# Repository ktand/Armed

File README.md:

# Armed 3D Printer Controller

## Features

* 32bit STM32F407VET6 
  * 168MHz 
  * 512kB Flash 
  * 192kB RAM 
* Power supply from 12-24V 
* Dual power inputs with separate fuses 
  * One for one of the high current outputs and the other one for the rest 
* Up to 5 steppers 
  * Dual outputs for one stepper for use with dual stepper Z-axis 
* 3 high current outputs 
* 3 fan outputs 
* 3 temperature sensors inputs 
* 3 endstops inputs 
* Filament runout detection 
* LCD display header 
* USB support 
* 10 extension pins 
* Support for TMC2130 SPI 
* 12-24V supply 
* I2C, SPI and UART extension ports 
* SWD header 
* Stepper configuration using solder jumpers 
* Einsy Rambo Form Factor (100x71mm) 

## Schematic and PCB Design

Designed using [Kicad 5.0](http://kicad.org/).

## Compatibilty

Arduino compatbile using the [Arduino Core STM32](https://github.com/stm32duino/Arduino_Core_STM32) and working with the [Marlin 2.0 3D printer firmware](https://github.com/MarlinFirmware/Marlin/tree/bugfix-2.0.x).

## Board configuration and pinout

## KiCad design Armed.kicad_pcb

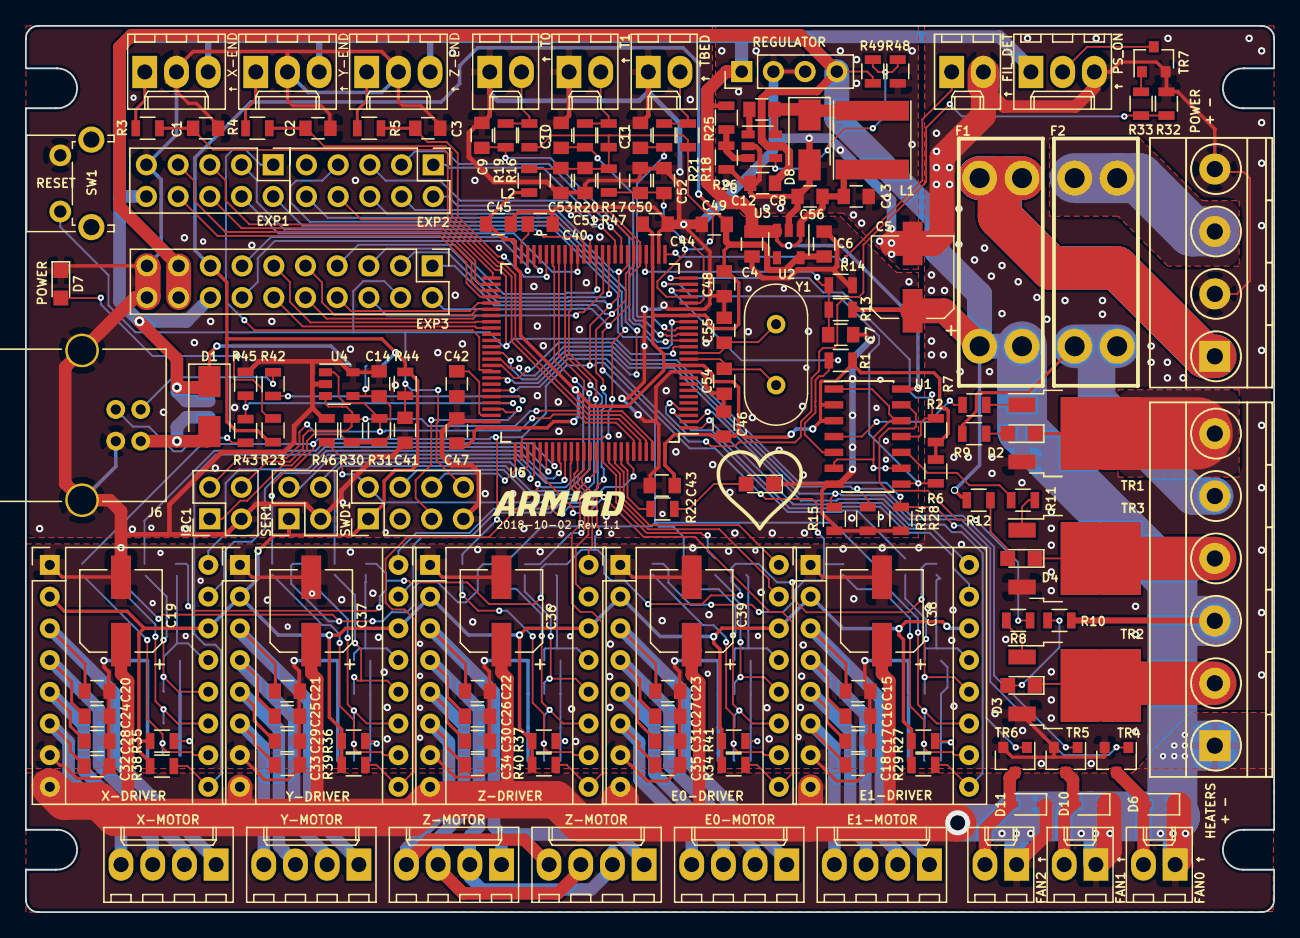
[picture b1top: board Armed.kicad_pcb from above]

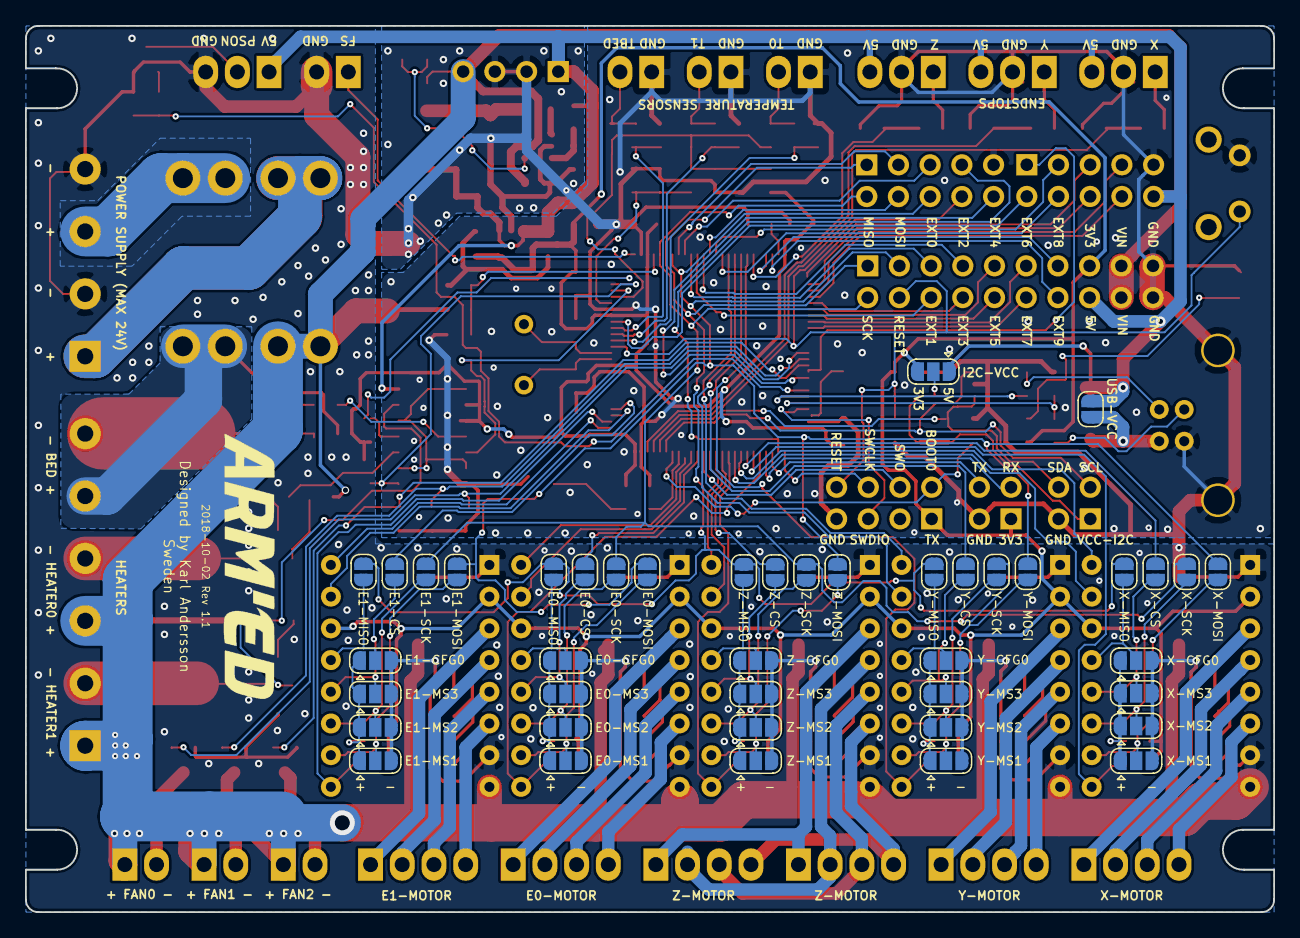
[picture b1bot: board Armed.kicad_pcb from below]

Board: 2 copper layers, 100.0 x 71.0 mm, 207 parts (42 on the bottom side), 165 nets.

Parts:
A1, A2, A3, A4, A5: Pololu_Breakout_A4988; Pololu_Breakout-16_15.2x20.3mm
C1, C2, C3: 10nF; C_0805
C4, C6: 1uF 16V X7R/X5R; C_0805
C5, C19, C36, C37, C38, C39: 100uF 35V; CP_Elec_6.3x5.8
C7, C12, C14, C41, C43, C44, C45, C46, C47, C48, C52, C53, C56: 100nF; C_0805
C8: 10uF 35V (X5R/X7R); C_0805
C9, C10, C11, C40, C42: 2.2uF; C_0805
C13: 10uF 16V (X5R/X7R); C_0805
C15, C16, C17, C18, C20, C21, C22, C23, C24, C25, C26, C27, C28, C29, C30, C31, C32, C33, C34, C35: 1nF; C_0805
C49: 10uF; C_0805
C50, C51: 1uF; C_0805
C54, C55: 20pF; C_0805
D1: BAT60J; D_SMA
D2, D3, D4, D5, D7: LED; LED_0805
D6, D10, D11: 1N4148WS; D_SOD-323
D8: B140-13-F; D_SMA
E0-MOT1, E1-MOT1: Conn_01x04_Male; Molex_KK-6410-04_04x2.54mm_Straight
EXP1, EXP2: Conn_02x05_Odd_Even; Pin_Header_Straight_2x05_Pitch2.54mm
EXP3: Conn_02x10_Odd_Even; Pin_Header_Straight_2x10_Pitch2.54mm
F1, F2: 3557-2; KEYSTONE-FUSE-3557-2
FAN1, FAN2, FAN3: Conn_01x02; Molex_KK-6410-02_02x2.54mm_Straight
FIL_DET1: Conn_01x02; Molex_KK-6410-02_02x2.54mm_Straight
I2C1: Conn_01x04; Pin_Header_Straight_2x02_Pitch2.54mm
J1: Conn_01x06; TerminalBlock_Phoenix_MKDS1.5-6pol
J2: Conn_01x04; TerminalBlock_Phoenix_MKDS1.5-4pol
J3, J4, J5: Conn_01x03; Molex_KK-6410-03_03x2.54mm_Straight
J6: USB_B
J7: Conn_01x04; Pin_Header_Straight_1x04_Pitch2.54mm
JP1: USB-VCC; SolderJumper-2_P1.3mm_Open_RoundedPad1.0x1.5mm
JP2: E1-MISO; SolderJumper-2_P1.3mm_Open_RoundedPad1.0x1.5mm
JP3: E1-MOSI; SolderJumper-2_P1.3mm_Open_RoundedPad1.0x1.5mm
JP4: E1-SCK; SolderJumper-2_P1.3mm_Open_RoundedPad1.0x1.5mm
JP5: E1-CS; SolderJumper-2_P1.3mm_Open_RoundedPad1.0x1.5mm
JP6: E1-CFG0; SolderJumper-3_P1.3mm_Open_RoundedPad1.0x1.5mm
JP7: E1-MS1; SolderJumper-3_P1.3mm_Open_RoundedPad1.0x1.5mm
JP8: E1-MS2; SolderJumper-3_P1.3mm_Open_RoundedPad1.0x1.5mm
JP9: E1-MS3; SolderJumper-3_P1.3mm_Open_RoundedPad1.0x1.5mm
JP10: E0-MISO; SolderJumper-2_P1.3mm_Open_RoundedPad1.0x1.5mm
JP11: E0-MOSI; SolderJumper-2_P1.3mm_Open_RoundedPad1.0x1.5mm
JP12: E0-SCK; SolderJumper-2_P1.3mm_Open_RoundedPad1.0x1.5mm
JP13: E0-CS; SolderJumper-2_P1.3mm_Open_RoundedPad1.0x1.5mm
JP14: X-MISO; SolderJumper-2_P1.3mm_Open_RoundedPad1.0x1.5mm
JP15: X-MOSI; SolderJumper-2_P1.3mm_Open_RoundedPad1.0x1.5mm
JP16: X-SCK; SolderJumper-2_P1.3mm_Open_RoundedPad1.0x1.5mm
JP17: X-CS; SolderJumper-2_P1.3mm_Open_RoundedPad1.0x1.5mm
JP18: Y-MISO; SolderJumper-2_P1.3mm_Open_RoundedPad1.0x1.5mm
JP19: Y-MOSI; SolderJumper-2_P1.3mm_Open_RoundedPad1.0x1.5mm
JP20: Y-SCK; SolderJumper-2_P1.3mm_Open_RoundedPad1.0x1.5mm
JP21: Y-CS; SolderJumper-2_P1.3mm_Open_RoundedPad1.0x1.5mm
JP22: Z-MISO; SolderJumper-2_P1.3mm_Open_RoundedPad1.0x1.5mm
JP23: Z-MOSI; SolderJumper-2_P1.3mm_Open_RoundedPad1.0x1.5mm
JP24: Z-SCK; SolderJumper-2_P1.3mm_Open_RoundedPad1.0x1.5mm
JP25: Z-CS; SolderJumper-2_P1.3mm_Open_RoundedPad1.0x1.5mm
JP26: E0-CFG0; SolderJumper-3_P1.3mm_Open_RoundedPad1.0x1.5mm
JP27: X-CFG0; SolderJumper-3_P1.3mm_Open_RoundedPad1.0x1.5mm
JP28: Y-CFG0; SolderJumper-3_P1.3mm_Open_RoundedPad1.0x1.5mm
JP29: Z-CFG0; SolderJumper-3_P1.3mm_Open_RoundedPad1.0x1.5mm
JP30: E0-MS1; SolderJumper-3_P1.3mm_Open_RoundedPad1.0x1.5mm
JP31: X-MS1; SolderJumper-3_P1.3mm_Open_RoundedPad1.0x1.5mm
JP32: Y-MS1; SolderJumper-3_P1.3mm_Open_RoundedPad1.0x1.5mm
JP33: Z-MS1; SolderJumper-3_P1.3mm_Open_RoundedPad1.0x1.5mm
JP34: X-MS2; SolderJumper-3_P1.3mm_Open_RoundedPad1.0x1.5mm
JP35: Y-MS2; SolderJumper-3_P1.3mm_Open_RoundedPad1.0x1.5mm
JP36: Z-MS2; SolderJumper-3_P1.3mm_Open_RoundedPad1.0x1.5mm
JP37: E0-MS2; SolderJumper-3_P1.3mm_Open_RoundedPad1.0x1.5mm
JP38: X-MS3; SolderJumper-3_P1.3mm_Open_RoundedPad1.0x1.5mm
JP39: Y-MS3; SolderJumper-3_P1.3mm_Open_RoundedPad1.0x1.5mm
JP40: Z-MS3; SolderJumper-3_P1.3mm_Open_RoundedPad1.0x1.5mm
JP41: E0-MS3; SolderJumper-3_P1.3mm_Open_RoundedPad1.0x1.5mm
JP42: I2C-VCC; SolderJumper-3_P1.3mm_Open_RoundedPad1.0x1.5mm
L1: 22uH NR6028T220M; L_Taiyo-Yuden_NR-60xx
L2: 7427920415; L_0805
PS_ON1: Conn_01x03; Molex_KK-6410-03_03x2.54mm_Straight
R1, R2, R6: 33k; R_0805
R3, R4, R5, R19, R20, R21, R29, R38, R39, R40, R41: 10k; R_0805
R7, R8, R11: 180; R_0805
R9, R10, R12, R14, R16, R17, R18, R27, R30, R31, R34, R35, R36, R37, R45: 4k7; R_0805
R13, R32, R48, R49: 47k; R_0805
R15, R22, R23, R24, R28, R33: 1k; R_0805
R25: 49.9k; R_0805
R26: 9.53k; R_0805
R42, R43: 20; R_0805
R44, R46: 100k; R_0805
R47: 47; R_0805
SER1: Conn_02x02; Pin_Header_Straight_2x02_Pitch2.54mm
SW1: SW_SPST; SW_Tactile_SPST_Angled_PTS645Vx31-2LFS
SWD1: Conn_02X04; Pin_Header_Straight_2x04_Pitch2.54mm
TEMP1, TEMP2, TEMP3: Conn_01x02; Molex_KK-6410-02_02x2.54mm_Straight
TR1, TR2, TR3: IPD036N04L; TO-252-2
TR4, TR5, TR6, TR7: PMV40UN2; SOT-23
U1: 74HCT02; SOIC-14_3.9x8.7mm_Pitch1.27mm
U2: AP2112K-3.3TRG1; SOT-23-5
U3: AOZ1282CI/AP3012; SOT-23-6
U4: 24LC32AT-I/OT; SOT-23-5
U5: STM32F407V(E-G)Tx; LQFP-100_14x14mm_Pitch0.5mm
X-MOT1: Conn_01x04_Male; Molex_KK-6410-04_04x2.54mm_Straight
Y1: 8MHz; Crystal_HC49-U_Vertical
Y-MOT1: Conn_01x04_Male; Molex_KK-6410-04_04x2.54mm_Straight
Z-MOT1, Z-MOT2: Conn_01x04_Male; Molex_KK-6410-04_04x2.54mm_Straight

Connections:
3V3_FAILURE: U1.1, U1.6, U1.9, U1.12
12V1: A1.8, A2.8, A3.8, A4.8, A5.8, C5.1, C8.1, C19.1, C36.1, C37.1, C38.1, C39.1, D6.1, D10.1, D11.1, EXP3.17, EXP3.18, F1.1, FAN1.1, FAN2.1, FAN3.1, J1.1, J1.3, J7.4, R10.2, R12.2, R13.1, R48.2, U3.5
12V2: F2.1, J1.5, R9.2
+3V3: A1.2, A1.14, A2.2, A2.14, A3.2, A3.14, A4.2, A4.14, A5.2, A5.14, C6.1, C43.2, C44.2, C45.2, C46.2, C47.2, C48.2, C49.2, EXP3.15, JP42.3, L2.2, R1.1, R2.1, R6.1, R23.1, R27.2, R29.1, R34.2, R35.2, R36.2, R37.2, R38.1, R39.1, R40.1, R41.1, R44.1, SER1.1, SWD1.1, U1.2, U1.3, U2.5, U5.11, U5.19, U5.28, U5.50, U5.75, U5.100
+5V: C4.1, C13.1, C56.1, D1.1, EXP1.10, EXP3.16, J3.3, J4.3, J5.3, J7.1, JP1.2, JP42.1, L1.1, PS_ON1.1, R25.1, U1.14, U2.1, U2.3
/VCC_I2C: C14.1, I2C1.1, JP42.2, R30.2, R31.2, U4.4
BEEPER_PIN: EXP1.1, U5.66
BOOT0: R46.2, SWD1.2, U5.94
BTN_ENC1: EXP1.2, U5.18
BTN_ENC2: EXP2.3, U5.33
BTN_ENC3: EXP2.5, U5.34
E0_CS_PIN: JP13.1, U5.90
E0_DIR_PIN: A5.16, U5.92
E0_ENABLE_PIN: A5.9, R41.2, U5.80
E0_STEP_PIN: A5.15, U5.91
E1_CS_PIN: JP5.1, U5.4
E1_DIR_PIN: A1.16, U5.1
E1_ENABLE_PIN: A1.9, R29.2, U5.2
E1_STEP_PIN: A1.15, U5.3
EXT0_PIN: EXP3.5, U5.35
EXT1_PIN: EXP3.6, U5.36
EXT2_PIN: EXP3.7, U5.37
EXT3_PIN: EXP3.8, U5.55
EXT4_PIN: EXP3.9, U5.56
EXT5_PIN: EXP3.10, U5.57
EXT6_PIN: EXP3.11, U5.58
EXT7_PIN: EXP3.12, U5.59
EXT8_PIN: EXP3.13, U5.47
EXT9_PIN: EXP3.14, U5.48
FAN0-: D6.2, FAN1.2, TR4.3
FAN0_PIN: R15.1, TR4.1, U5.63
FAN1-: D10.2, FAN2.2, TR5.3
FAN1_PIN: R24.1, TR5.1, U5.64
FAN2-: D11.2, FAN3.2, TR6.3
FAN2_PIN: R28.1, TR6.1, U5.65
FILAMENT_PIN: FIL_DET1.1, U5.26
GND: A1.1, A1.7, A2.1, A2.7, A3.1, A3.7, A4.1, A4.7, A5.1, A5.7, C1.2, C2.2, C3.2, C4.2, C5.2, C6.2, C7.2, C8.2, C9.2, C10.2, C11.2, C13.2, C14.2, C15.2, C16.2, C17.2, C18.2, C19.2, C20.2, C21.2, C22.2, C23.2, C24.2, C25.2, C26.2, C27.2, C28.2, C29.2, C30.2, C31.2, C32.2, C33.2, C34.2, C35.2, C36.2, C37.2, C38.2, C39.2, C40.1, C41.2, C42.1, C43.1, C44.1, C45.1, C46.1, C47.1, C48.1, C49.1, C50.1, C51.2, C52.1, C53.2, C54.1, C55.1, C56.2, D5.1, D7.1, D8.2, EXP1.9, EXP2.9, EXP3.19, EXP3.20, FIL_DET1.2, I2C1.3, J2.2, J2.4, J3.2, J4.2, J5.2, J6.4, J6.5, J7.2, J7.3, JP6.3, JP7.3, JP8.3, JP9.3, JP26.3, JP27.3, JP28.3, JP29.3, JP30.3, JP31.3, JP32.3, JP33.3, JP34.3, JP35.3, JP36.3, JP37.3, JP38.3, JP39.3, JP40.3, JP41.3, PS_ON1.3, R14.2, R15.2, R24.2, R26.2, R28.2, R32.2, R45.1, R46.1, R49.1, SER1.3, SW1.2, SWD1.7, TEMP1.1, TEMP2.1, TEMP3.1, TR1.3, TR2.3, TR3.3, TR4.2, TR5.2, TR6.2, TR7.2, U1.7, U2.2, U3.2, U4.2, U4.5, U5.10, U5.20, U5.27, U5.74, U5.99
HEATBED-: D2.1, J1.6, TR1.2
HEATER0-: D4.1, J1.4, TR3.2
HEATER1-: D3.1, J1.2, TR2.2
HEATER_0_PIN: R6.2, U1.8, U5.24
HEATER_1_PIN: R2.2, U1.11, U5.25
HEATER_BED_PIN: R1.2, U1.5, U5.23
KILL_PIN: EXP2.10, U5.67
LCD_PINS_D4: EXP1.5, U5.51
LCD_PINS_D5: EXP1.6, U5.52
LCD_PINS_D6: EXP1.7, U5.53
LCD_PINS_D7: EXP1.8, U5.54
LCD_PINS_ENABLE: EXP1.3, U5.39
LCD_PINS_RS: EXP1.4, U5.40
LED_PIN: R22.1, U5.93
unnamed: A1.3, C15.1, E1-MOT1.1
unnamed: A1.4, C16.1, E1-MOT1.2
unnamed: A1.5, C17.1, E1-MOT1.3
unnamed: A1.6, C18.1, E1-MOT1.4
unnamed: A1.10, JP3.2, JP7.2
unnamed: A1.11, JP4.2, JP8.2
unnamed: A1.12, JP5.2, JP9.2
unnamed: A1.13, JP2.2, JP6.2
unnamed: A2.3, C20.1, X-MOT1.1
unnamed: A2.4, C24.1, X-MOT1.2
unnamed: A2.5, C28.1, X-MOT1.3
unnamed: A2.6, C32.1, X-MOT1.4
unnamed: A2.10, JP15.2, JP31.2
unnamed: A2.11, JP16.2, JP34.2
unnamed: A2.12, JP17.2, JP38.2
unnamed: A2.13, JP14.2, JP27.2
unnamed: A3.3, C21.1, Y-MOT1.1
unnamed: A3.4, C25.1, Y-MOT1.2
unnamed: A3.5, C29.1, Y-MOT1.3
unnamed: A3.6, C33.1, Y-MOT1.4
unnamed: A3.10, JP19.2, JP32.2
unnamed: A3.11, JP20.2, JP35.2
unnamed: A3.12, JP21.2, JP39.2
unnamed: A3.13, JP18.2, JP28.2
unnamed: A4.3, C22.1, Z-MOT1.1, Z-MOT2.1
unnamed: A4.4, C26.1, Z-MOT1.2, Z-MOT2.2
unnamed: A4.5, C30.1, Z-MOT1.3, Z-MOT2.3
unnamed: A4.6, C34.1, Z-MOT1.4, Z-MOT2.4
unnamed: A4.10, JP23.2, JP33.2
unnamed: A4.11, JP24.2, JP36.2
unnamed: A4.12, JP25.2, JP40.2
unnamed: A4.13, JP22.2, JP29.2
unnamed: A5.3, C23.1, E0-MOT1.1
unnamed: A5.4, C27.1, E0-MOT1.2
unnamed: A5.5, C31.1, E0-MOT1.3
unnamed: A5.6, C35.1, E0-MOT1.4
unnamed: A5.10, JP11.2, JP30.2
unnamed: A5.11, JP12.2, JP37.2
unnamed: A5.12, JP13.2, JP41.2
unnamed: A5.13, JP10.2, JP26.2
unnamed: C12.1, U3.1
unnamed: C12.2, D8.1, L1.2, U3.6
unnamed: C54.2, U5.12, Y1.1
unnamed: C55.2, U5.13, Y1.2
unnamed: D1.2, J6.1, JP1.1
unnamed: D2.2, R9.1
unnamed: D3.2, R10.1
unnamed: D4.2, R12.1
unnamed: D5.2, R22.2
unnamed: D7.2, R23.2
unnamed: J3.1, R3.2
unnamed: J4.1, R4.2
unnamed: J5.1, R5.2
unnamed: JP6.1, JP7.1, JP8.1, JP9.1, R27.1
unnamed: JP26.1, JP30.1, JP37.1, JP41.1, R34.1
unnamed: JP27.1, JP31.1, JP34.1, JP38.1, R35.1
unnamed: JP28.1, JP32.1, JP35.1, JP39.1, R36.1
unnamed: JP29.1, JP33.1, JP36.1, JP40.1, R37.1
unnamed: R7.1, TR1.1
unnamed: R7.2, U1.4
unnamed: R8.1, TR2.1
unnamed: R8.2, U1.13
unnamed: R11.1, TR3.1
unnamed: R11.2, U1.10
unnamed: R16.2, R19.2, TEMP1.2
unnamed: R17.2, R20.2, TEMP2.2
unnamed: R18.2, R21.2, TEMP3.2
unnamed: R25.2, R26.1, U3.3
unnamed: R33.1, TR7.1
unnamed: R42.1, U5.70
unnamed: R43.1, R45.2, U5.71
unnamed: R48.1, R49.2, U3.4
POWER_MONITOR: C7.1, R13.2, R14.1, U5.29
PS_ON: PS_ON1.2, TR7.3
PS_ON_PIN: R32.1, R33.2, U5.69
RESET: C41.1, EXP2.8, EXP3.4, R44.2, SW1.1, SWD1.8, U5.14
RX_PIN: SER1.2, U5.79
SCL: I2C1.2, R31.1, U4.1, U5.95
SDA: I2C1.4, R30.1, U4.3, U5.96
SD_CS: EXP2.4, U5.38
SD_DETECT_PIN: EXP2.7, U5.77
SPI_MISO: EXP2.1, EXP3.1, JP2.1, JP10.1, JP14.1, JP18.1, JP22.1, U5.31
SPI_MOSI: EXP2.6, EXP3.3, JP3.1, JP11.1, JP15.1, JP19.1, JP23.1, U5.32
SPI_SCK: EXP2.2, EXP3.2, JP4.1, JP12.1, JP16.1, JP20.1, JP24.1, U5.30
SWCLK: SWD1.6, U5.76
SWDIO: SWD1.5, U5.72
SWO: SWD1.4, U5.89
TEMP_0_PIN: C9.1, R19.1, U5.15
TEMP_1_PIN: C10.1, R20.1, U5.16
TEMP_2_PIN: C11.1, R21.1, U5.17
TX_PIN: SER1.4, U5.78
USB_DM: J6.2, R42.2
USB_DP: J6.3, R43.2
VCAP_1: C40.2, U5.49
VCAP_2: C42.2, U5.73
VDDA: C51.1, C53.1, L2.1, R16.1, R17.1, R18.1, R47.2, U5.22
VIN1: F1.2, J2.1
VIN2: F2.2, J2.3
VREF+: C50.2, C52.2, R47.1, U5.21
X_CS_PIN: JP17.1, U5.82
X_DIR_PIN: A2.16, U5.83
X_ENABLE_PIN: A2.9, R38.2, U5.81
X_MIN_PIN: C1.1, R3.1, U5.97
X_STEP_PIN: A2.15, U5.84
Y_CS_PIN: JP21.1, U5.43
Y_DIR_PIN: A3.16, U5.41
Y_ENABLE_PIN: A3.9, R39.2, U5.44
Y_MIN_PIN: C2.1, R4.1, U5.98
Y_STEP_PIN: A3.15, U5.42
Z_CS_PIN: JP25.1, U5.86
Z_DIR_PIN: A4.16, U5.88
Z_ENABLE_PIN: A4.9, R40.2, U5.85
Z_MIN_PIN: C3.1, R5.1, U5.45
Z_STEP_PIN: A4.15, U5.87

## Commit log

2018-11-14 Armed 1.0 Schematic/PCB
2018-11-14 Armed 1.0 Board rendering
2018-11-14 Armed 1.1
2018-11-14 Updated to match Armed 1.1
2018-11-14 Updated board images
2021-01-22 Fixed library references
2021-11-08 Update README.md
    https://forum.kicad.info/t/warning-avoid-all-links-to-kicad-pcb-org-use-kicad-org/31521
